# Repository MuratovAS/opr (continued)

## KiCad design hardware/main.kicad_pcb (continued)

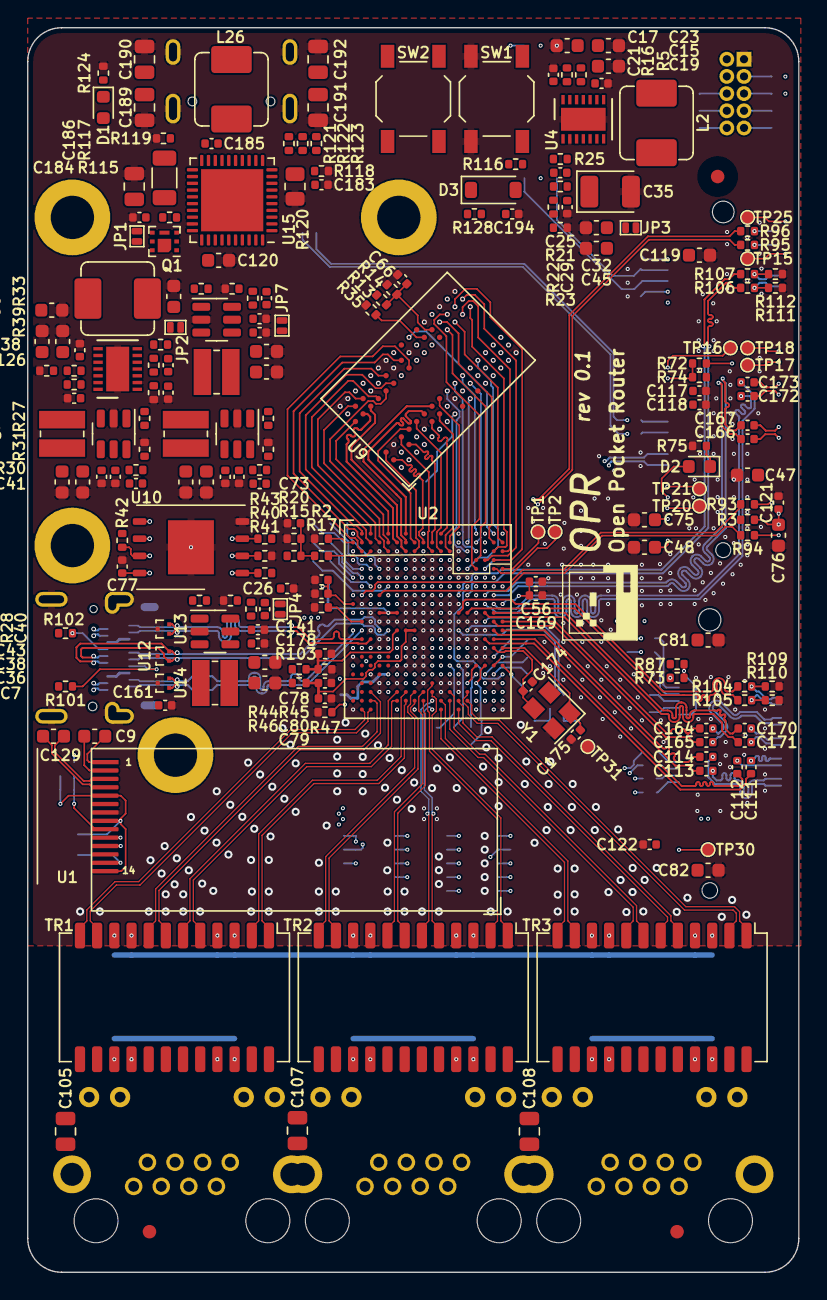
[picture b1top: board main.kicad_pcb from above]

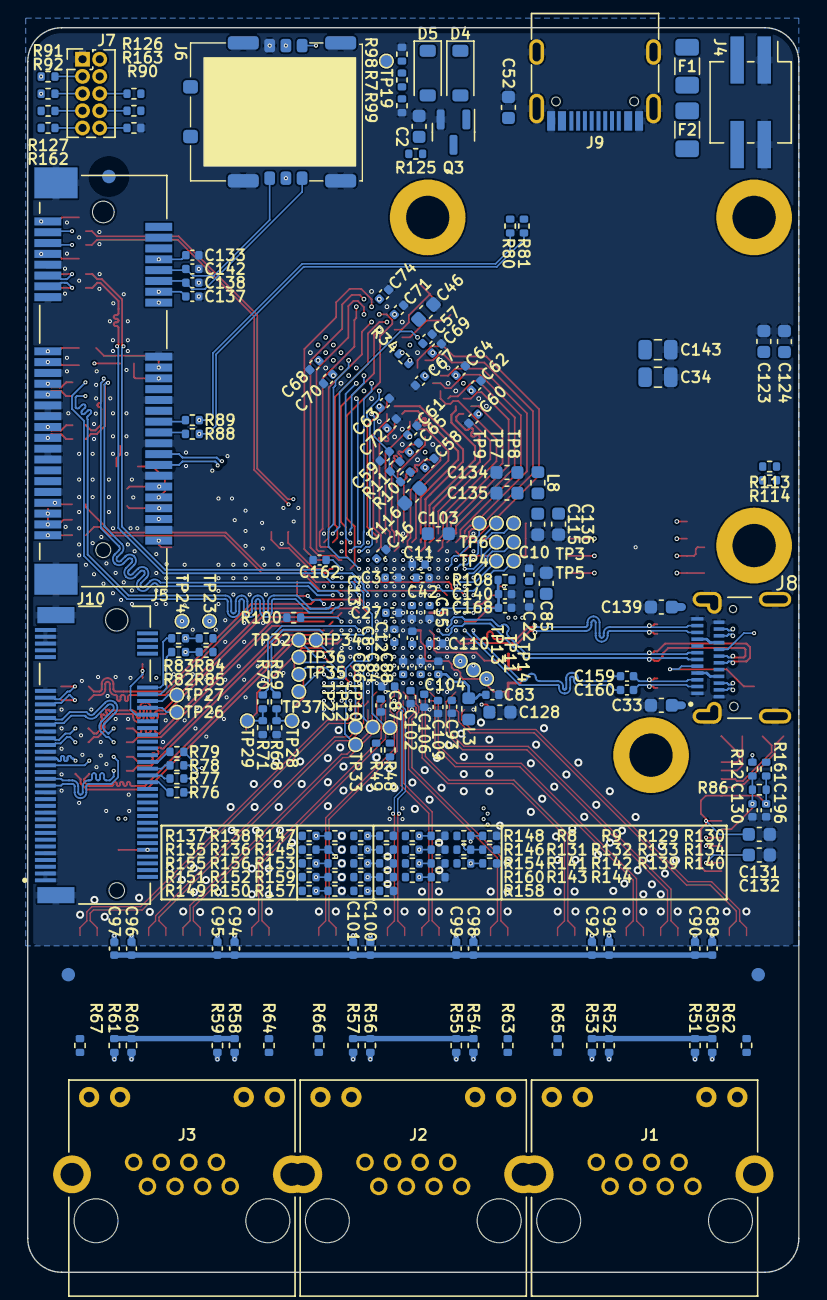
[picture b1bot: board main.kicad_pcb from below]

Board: 6 copper layers, 57.0 x 92.0 mm, 432 parts (217 on the bottom side), 366 nets.

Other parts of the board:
J6: 1042240820
R74: 4.7k; R_0402_1005Metric

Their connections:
+3V3: R74.2; also elsewhere on the board

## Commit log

2022-12-12 ad dcdc
2022-12-13 update dcdc
2022-12-14 add eth and usb
2022-12-14 clear
2022-12-15 add ram and rom
2022-12-16 add pin layout ram and usb
2022-12-18 add cpu and pin layout
2022-12-22 add mt7603
2022-12-23 add rf
2022-12-24 add oled
2022-12-24 init pcb
2022-12-24 update pcb
2022-12-26 trace ram
2023-02-27 Create LICENSE
2023-05-05 fix pcb
2023-09-07 update cap and dru
2023-09-07 add mini-pcie and m2
2023-09-08 add mPCI-e and m2 conn
2023-09-08 pinlayout for pci-e
2023-09-09 circuits are combined
2023-09-10 update 100923
2023-09-10 update sch
2023-09-10 update outline
2023-09-12 updated rules for differential pairs
2023-09-12 calc Impedance and mark wire
2023-09-13 update pin layout
2023-09-13 update silk
2023-09-13 fix silk
2023-09-13 examples removed
2023-09-15 custom layout ddr3
2023-09-16 fixed gap on ddr lines
2023-09-16 fixed ddr tracing, usb tracing
2023-09-16 track tracing
2023-09-17 eth tracing
2023-09-18 update vias
2023-09-18 impedance matching
2023-09-20 trace completed
2023-09-20 update dru
2023-09-20 add JLC Order Number
2023-09-20 fix mask via for bga
2023-09-22 ddr3 impedance matched
2023-09-22 fix `Hole to hole clearance(Different nets)`
2023-09-23 fix `Via to Track`
2023-09-23 add usb hub and wifi
2023-09-23 update img
2023-10-01 fix U.FL_Hirose
2023-10-04 fix drc; add fasteners
2023-10-22 fix prj; description -> Comments
2023-10-28 close #4
2023-10-28 close #5
2023-10-28 close #3
2024-04-22 add case
